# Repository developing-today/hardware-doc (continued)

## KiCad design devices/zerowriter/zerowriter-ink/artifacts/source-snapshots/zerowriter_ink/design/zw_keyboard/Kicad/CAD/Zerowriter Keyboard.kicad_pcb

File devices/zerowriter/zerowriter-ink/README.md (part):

# ZeroWriter Ink

> Open-source e-paper typewriter · Crowd Supply campaign funded **2024-10-17** · **$285** · 585 backers · $147,538 raised (491 % of a $30,000 goal)
> By **Adam Wilk** / Zerowriter, Ottawa, Canada, in collaboration with **Soldered Electronics** (Osijek, Croatia)
> Research snapshot **2026-08-24**

A distraction-free writing device: a 5.2" 1280×720 e-paper display, a hot-swappable 60 % mechanical keyboard, and firmware that boots straight into a text file. No cloud, no accounts, no wireless enabled by default.

---

## The single most important architectural fact

**ZeroWriter Ink contains two ESP32s.**

| Board | Processor | Role |
|---|---|---|
| **Zerowriter Inkplate 5 Gen2** (main board) | **ESP32-WROVER** | Display, storage, RTC, application firmware |
| **Zerowriter Keyboard** (keyboard PCB) | **ESP32-WROOM-32U-N4** | Key-matrix scanning, its own firmware |

This is recovered from the two KiCad BOMs in the project's own repository ([`design/src/`](artifacts/source-snapshots/zerowriter_ink/design/src/)) and is **not stated anywhere in the campaign material or the README**, which describe the device as "built around the ubiquitous ESP32 module" — singular. If you are planning firmware work, you need to know there are two independent targets joined by a cable.

The keyboard PCB carries a `NOVA_programmer_header` (6-pin) and connects to the main board through a **`HC-1.25-6PWT` 6-pin connector**, which strongly suggests a serial link rather than a scanned matrix crossing the cable — 61 × `1N4148W` matrix diodes are on the *keyboard* board, so the matrix is decoded locally.

> Evidence status: the two-processor split is **established from primary design files**. The *protocol* between them is **inferred** from connector pin count and the placement of the matrix diodes — not confirmed from source.

---

## The second important fact: this is not a stock Inkplate 5

ZeroWriter's main board is a **respin** of Soldered's Inkplate 5 Gen 2, not the off-the-shelf product. Comparing the two BOMs designator-by-designator ([Soldered Gen 2](../../soldered-electronics/inkplate-5-gen2/README.md) vs [ZeroWriter's variant](artifacts/source-snapshots/zerowriter_ink/design/src/)) shows **8 added parts, 14 removed, and 20 changed values**.

### Which Inkplate generation? — **Gen 2**, confirmed five ways

Worth stating plainly, because the campaign's early material described a different panel (see below).

| Evidence | Result |
|---|---|
| ZeroWriter BOM, `U9` | **`ED052TC4`** |
| Soldered Inkplate 5 **Gen 2** BOM, `U9` | `ED052TC4` ✅ match |
| Soldered Inkplate 5 (gen 1) BOM, `U11` | `ED052TC2` ❌ different part *and* different designator |
| ZeroWriter's KiCad project name | `Zerowriter Inkplate 5 **Gen2**.kicad_pro` |
| Crowd Supply spec | "**second-edition** Inkplate 5.2" display with an upgraded **1280 × 720** widescreen resolution" |
| Campaign update, Nov 2024 | "we jumped on their **new generation panel: Inkplate 5v2**" |

`ED052TC4` ⇒ **1280 × 720** (`ARDUINO_INKPLATE5V2`). The gen-1 `ED052TC2` is 960 × 540.

#### ⚠ The panel changed mid-project

If you recall the ZeroWriter Ink being a **gen-1** Inkplate 5, that was true of the **development prototype**. The developer describes the switch in the Nov 2024 post-funding update:

> When it came to Zerowriter Ink, **we jumped on their new generation panel: Inkplate 5v2**… The downside? … The new panels looked great, but operated at about 200 ms. This was **a decent chunk slower than the panel I'd been developing into Zerowriter Ink**…

So the sequence was: prototype on the **gen-1 panel** → switch to **Gen 2** for the higher resolution → discover it is slower → commission [bitbank2's optimisation work](development-history.md#the-e-paper-latency-problem-and-how-it-was-solved) to get from ~200 ms to ~100 ms.

**The shipping product is Gen 2.** Pre-funding material describing a 960 × 540 panel is describing the prototype.

### "Minor tweaks" is an understatement

The respin is not a light touch. Designator-by-designator against Soldered's stock Gen 2: **8 parts added, 14 removed, 20 values changed**, including a complete charger redesign and relocation of USB-C and microSD to a separate board.

What *is* unchanged is the part that matters for software: **all 36 connected ESP32 pads carry identical net names** ([verified](../../soldered-electronics/inkplate-5-gen2/README.md#zerowriter-compatibility)), so the Inkplate Arduino library applies. That is probably the origin of the "minor tweaks" impression — from a firmware perspective it behaves like a stock Gen 2; from a hardware perspective it is substantially reworked.

### The charger was completely redesigned

| | Soldered Inkplate 5 Gen 2 | **ZeroWriter variant** |
|---|---|---|
| Charger IC | `MCP73831T` — **linear** | **`BQ25306RTER`** — TI **switch-mode** buck charger |
| Inductor | — | **`L3 = SRP3212A-1R0M`** (1 µH) added |
| Support caps | — | `C58` 4u7, `C59` 2u2, `C60`/`C61` 10u, `C62` 470p added |
| `U4` position | `MCP73831T` (charger) | **`USBLC6-2SC6`** — USB ESD protection |

A linear charger dissipates `(Vin − Vbat) × Icharge` as heat, which caps practical charge current on a small board. Swapping to a switch-mode `BQ25306` is exactly what you do when you fit a much larger cell and want it charged in reasonable time without cooking the PCB. This is consistent with the campaign's "up to weeks of daily use" and ~100 hour battery-life claim.

### Connectors moved off the display board

| Ref | Soldered Gen 2 | ZeroWriter variant | Reading |
|---|---|---|---|
| `K2` | `U262-161N-4BVC11` (**USB-C receptacle**) | `HC-1.25-6PWT` (**6-pin wire-to-board**) | USB-C is **not on the display board** — it moves to the separate breakout PCB |
| `K1` | — | `HC-1.25-16PWT` (**16-pin**) added | New inter-board link |
| `K3` | `easyC-SMD` | `qwiic-SMD` | Same physical connector, renamed. Soldered's *easyC* is pin-compatible with SparkFun *Qwiic* / Adafruit *STEMMA QT* |
| `K10` | `HYC77-TF09-200` (**microSD socket**) | *removed* | microSD relocated off the display board |

### Parts removed

`U5` (`MC14093BDTR2G` quad Schmitt NAND), `F1` (500 mA fuse), `D8`/`D9` (LEDs), `SW2` (button), `S1` (slide switch), `Q8`/`Q9`, and test points `TP60`–`TP63`. Plus ~20 resistor/capacitor value changes clustered around the power and charging sections.

**Consequence for hackers:** a stock Inkplate 5 Gen 2 is *close* to the ZeroWriter main board but not identical. Firmware written against the Inkplate Arduino library should work (same ESP32-WROVER, same `ED052TC4` panel, same `TPS65186` PMIC, same `PCAL6416A` expander, same `PCF85063A` RTC), but **power, charging, USB and SD paths differ** — do not assume battery or SD behaviour transfers.

---

## Architecture

```
┌─ Zerowriter Keyboard PCB ──────────────────────────────┐
│ ESP32-WROOM-32U-N4  (external-antenna variant)         │
│ 61 × 1N4148W matrix diodes                             │
│ Kailh Choc v1 hot-swap sockets (CPG135001S30)          │
│   incl. 1.2u / 1.5u / 1.7u / 2u / 6.25u stabilised keys│
│ RST1/RST2 tactiles · NOVA 6-pin programmer header      │
└────────────── HC-1.25-6PWT (6-pin) ────────────────────┘
                       │
┌─ Zerowriter Inkplate 5 Gen2 (main) ────────────────────┐
│ ESP32-WROVER              U11                          │
│ ED052TC4  5.2" 1280×720 e-paper   U9                   │
│ TPS65186RGZ  e-paper PMIC          U1                  │
│ PCAL6416AHF  16-bit I²C GPIO expander @ 0x20  U10      │
│ PCF85063A    RTC                    U7                 │
│ CH340C       USB-UART               U3                 │
│ BQ25306RTER  switch-mode Li-ion charger  U12  [ZW-only]│
│ TPS7A2633    3V3 LDO · TPS3840 supervisor              │
│ qwiic/easyC I²C connector                              │
└──── HC-1.25-16PWT (16-pin) ────────────────────────────┘
                       │
┌─ Zerowriter breakout board ────────────────────────────┐
│ USB-C, microSD (relocated from the display board)      │
└────────────────────────────────────────────────────────┘
```

Component records: [ESP32-WROVER](../../../components/espressif/esp32-wrover/README.md) · [ESP32-WROOM-32U](../../../components/espressif/esp32-wroom-32u/README.md) · [TPS65186](../../../components/texas-instruments/tps65186/README.md) · [PCAL6416A](../../../components/nxp/pcal6416a/README.md) · [PCF85063A](../../../components/nxp/pcf85063a/README.md) · [BQ25306](../../../components/texas-instruments/bq25306/README.md) · [CH340C](../../../components/wch/ch340c/README.md) · [ED052TC4 panel](../../../components/e-ink/ed052tc4/README.md)

## Specifications

| | |
|---|---|
| Display | **Inkplate 5 Gen 2 panel — `ED052TC4`, 5.2", 1280 × 720** e-paper |
| Keyboard | 60 %, hot-swappable, **Kailh Choc Pro Red** low-profile switches, US English legends, optional arrow-key mod |
| Languages | Extended ASCII 256 — English, French, German, Spanish, Italian and other western/latin scripts |
| Dimensions | **300 × 195 × 15 mm** (12 × 7.5 × 0.6 in) — fits most 13" laptop sleeves |
| Storage | microSD (user files), plus firmware update via SD |
| Connectivity | USB-C (charging + UART file transfer via companion app); **QR-code transfer to phone**; Wi-Fi/BLE present in silicon but **not enabled in shipped firmware** |
| Battery | Built-in, **user-replaceable** LiPo; ~100 h claimed |
| Document limit | **3,000 lines (~24,000 words)** per document |
| Firmware | Arduino-based ("Zerowriter Core"). Repo releases end at **1.30**; **current is v2.1 (July 2026)**, website-only — see [`community-and-ecosystem.md`](community-and-ecosystem.md#-the-repository-firmware-is-two-major-versions-behind) |
| Enclosure | Custom; STLs in-repo (`zw_tophousing.stl`, `zw_bottomhousing.stl`) |

**On wireless:** the campaign is explicit that shipping without wireless was a deliberate cost/certification decision — "less development time, less red-tape, and less cost to you" — not a hardware limitation. Note the keyboard uses a **WROOM-32U**, the *external antenna* variant, which has no PCB antenna at all. Enabling radio on either processor is a project, not a config flag.

## Vendor comparison (from the campaign)

| | Zerowriter Ink | Pomera DM30 | Alphasmart Neo | Freewrite Alpha | Freewrite Traveler |
|---|---|---|---|---|---|
| Display | **HD e-paper** | e-paper | LCD | LCD | e-paper |
| Cloud | Not by default | No | No | Yes | Yes |
| Availability | **New** | Used | Used | New | New |
| Mechanical keyboard | **Yes, hot-swap** | No | No | Yes | No |
| Battery (claimed) | 100 h | 20 h | **700 h** | 100 h | 4 weeks |
| Open source | **Yes** | No | No | No | No |

Vendor-authored comparison — treat as marketing. The Alphasmart Neo's 700 hours on AA cells is the honest outlier and the standard this class of device is measured against.

## Lineage

The **original ZeroWriter** ([`zerowriter/zerowriter1`](artifacts/source-snapshots/zerowriter1/), 367★, MIT) was a Raspberry Pi Zero + cheap e-paper DIY project. ZeroWriter Ink is a ground-up redesign on the Inkplate 5 — a different processor family, a different display, and a commercial product rather than a build-it-yourself guide. The two share a name and a goal, not a codebase.

## Website: zerowriter.**ink**, not .com

⚠ **`zerowriter.com` is a domain-for-sale parking page** (Spaceship.com, $7,500) and is *not* the project. The Crowd Supply campaign links to it, so it is an easy trap.

**The live site is <https://zerowriter.ink>.** Found via a URL embedded in the firmware release notes shipped in the GitHub repo (`firmware_releases/updates-readme.txt` points at `zerowriter.ink/pages/firmware-updates`), not from any link on the campaign page.

The live site reveals a **second product**: the **Zerowriter Fold**, funded via Kickstarter and shipping after the Ink.

| Source | URL | Status |
|---|---|---|
| **Official site** | <https://zerowriter.ink> | **Live** |
| Firmware updates + web flasher | <https://zerowriter.ink/pages/firmware-updates> | **Live** |
| News blog | <https://zerowriter.ink/blogs/news> | Live |
| Zerowriter Fold | <https://zerowriter.ink/pages/zerowriter-fold> | Live |
| Crowd Supply campaign | <https://www.crowdsupply.com/zerowriter/zerowriter-ink> | Live |
| GitHub (main) | <https://github.com/zerowriter/zerowriter_ink> | Live, GPL-3.0 |
| GitHub (original Pi project) | <https://github.com/zerowriter/zerowriter1> | Live, MIT |
| Discord | <https://discord.gg/57yANTWGet> | Live |
| **Reddit** | <https://www.reddit.com/r/zerowriter/> | Live — official support channel |
| `zerowriter.com` | — | **Parked / for sale. Not the project.** |

> **Retrieval trap:** `zerowriter.ink` returns **403 to a normal Chrome user agent** but **200 to the ClaudeBot UA**. See the [vendor guide](../../../vendors/zerowriter/README.md).

## Press coverage

Tom's Hardware · Liliputing · Boing Boing · Yanko Design · Notebookcheck (DE) · CircuitDigest · TechEBlog · Good e-Reader · e-ink-info · ereaderpro.co.uk · pascalforget.com — full URLs in [`sources.md`](sources.md).

## Repository contents (preserved)

```
artifacts/source-snapshots/zerowriter_ink/     GPL-3.0, commit 996207ac (2026-05-13)
├── design/
│   ├── src/Zerowriter Inkplate 5 Gen2/v1.2.0/   KiCad: main board respin
│   ├── src/Zerowriter Keyboard/v1.2.0/          KiCad: keyboard + ESP32-WROOM-32U
│   ├── src/Zerowriter breakout board/           gerbers: USB-C + microSD
│   ├── zw_keyboard/                             plate DXF, gerbers, schematic PDF
│   └── enclosure/                               zw_tophousing.stl, zw_bottomhousing.stl
├── firmware_releases/                           SD-1.3, archived updates, CLI tools
├── compiled fonts/                              .bbf bitmap fonts
├── src/keyboard/                                keyboard firmware source
└── utils/
artifacts/source-snapshots/zerowriter1/        MIT, commit e476d056 — the Pi Zero original
```

### Size cleanup — what was moved out (2026-08-24)

Two things were archived out of this tree. **Both left a placeholder in situ** carrying digests and
reacquisition commands, and neither is unique:

| Removed | Size | Placeholder | Why it was safe |
|---|---:|---|---|
| `zerowriter1/e-Paper/` — Waveshare's vendored Python driver library | 31.07 MiB, 272 files | [`e-Paper.ARCHIVED.md`](artifacts/source-snapshots/zerowriter1/e-Paper.ARCHIVED.md) | 270 of 272 files byte-identical to Waveshare upstream; the 2 that differ are preserved as patches |
| 4 × KiCad `*-backups/` auto-save ZIP directories | 27.27 MiB, 15 files | one `*.ARCHIVED.md` beside each | editor crash-recovery snapshots of designs that are still present, uncompressed, alongside |

**No design file, firmware image or ZeroWriter-authored source was removed.** All 15 backup ZIPs
are present in the archive and recoverable verbatim from upstream commit `996207ac`
(re-verified **2026-09-20**, see below).

> ⚠ **Corrected 2026-09-20.** This section previously asserted that the entire `zerowriter_ink`
> snapshot "was verified **byte-identical** to upstream commit `996207ac`". That was true when
> written on 2026-08-24 and **is no longer true of the tree today**: on 2026-08-30 an in-repo pass
> normalised **50 of the snapshot's 152 files** — 36 CRLF → LF, 14 trailing-whitespace-stripped.
> **Zero semantic differences** were introduced, so every pinout, net and BOM row read out of these
> files remains sound; but `diff -rq` and raw SHA-256 comparison against upstream will now report
> 50 false positives, and an in-repo file hash must not be cited as upstream identity.
> Full file-by-file breakdown, cause analysis and the correct comparison recipe:
> **[`source-snapshot-provenance.md`](source-snapshot-provenance.md)**.
>
> The same document records that three of the four `*-backups/` directories had been lost from the
> archive (a later pass archived their parent `PANEL/` onto the same path) and survived only in
> `scratch/`. They were moved back into the archive on 2026-09-20 and verified by fingerprint.

- [`artifacts/vendored-deps/README.md`](artifacts/vendored-deps/README.md) — removed-dependency register: digests, licenses, verified download URLs
- [`zerowriter1-epaper-driver-notes.md`](zerowriter1-epaper-driver-notes.md) — **what ZeroWriter changed in the Waveshare driver, and why it matters**
- [`source-snapshot-provenance.md`](source-snapshot-provenance.md) — **what is and is not byte-identical to upstream in this snapshot**, and how to compare it correctly

## Related

- [Inkplate 5 / Gen 2](../../soldered-electronics/inkplate-5/README.md) — the display platform this is built on
- [Soldered Electronics vendor guide](../../../vendors/soldered-electronics/README.md)
- [All devices](../../README.md)
- [`keyboard.md`](keyboard.md) — the second ESP32, wire protocol, matrix
- [`inter-board-wiring.md`](inter-board-wiring.md) — both connector pinouts, breakout board BOM
- [`keymap-format.md`](keymap-format.md) — `keymap.json`, full default layout
- [`software-and-shortcuts.md`](software-and-shortcuts.md) — shortcuts, Core 1.1, release timeline
- [`community-and-ecosystem.md`](community-and-ecosystem.md) — **firmware v2.1**, third-party firmware, owner reports
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
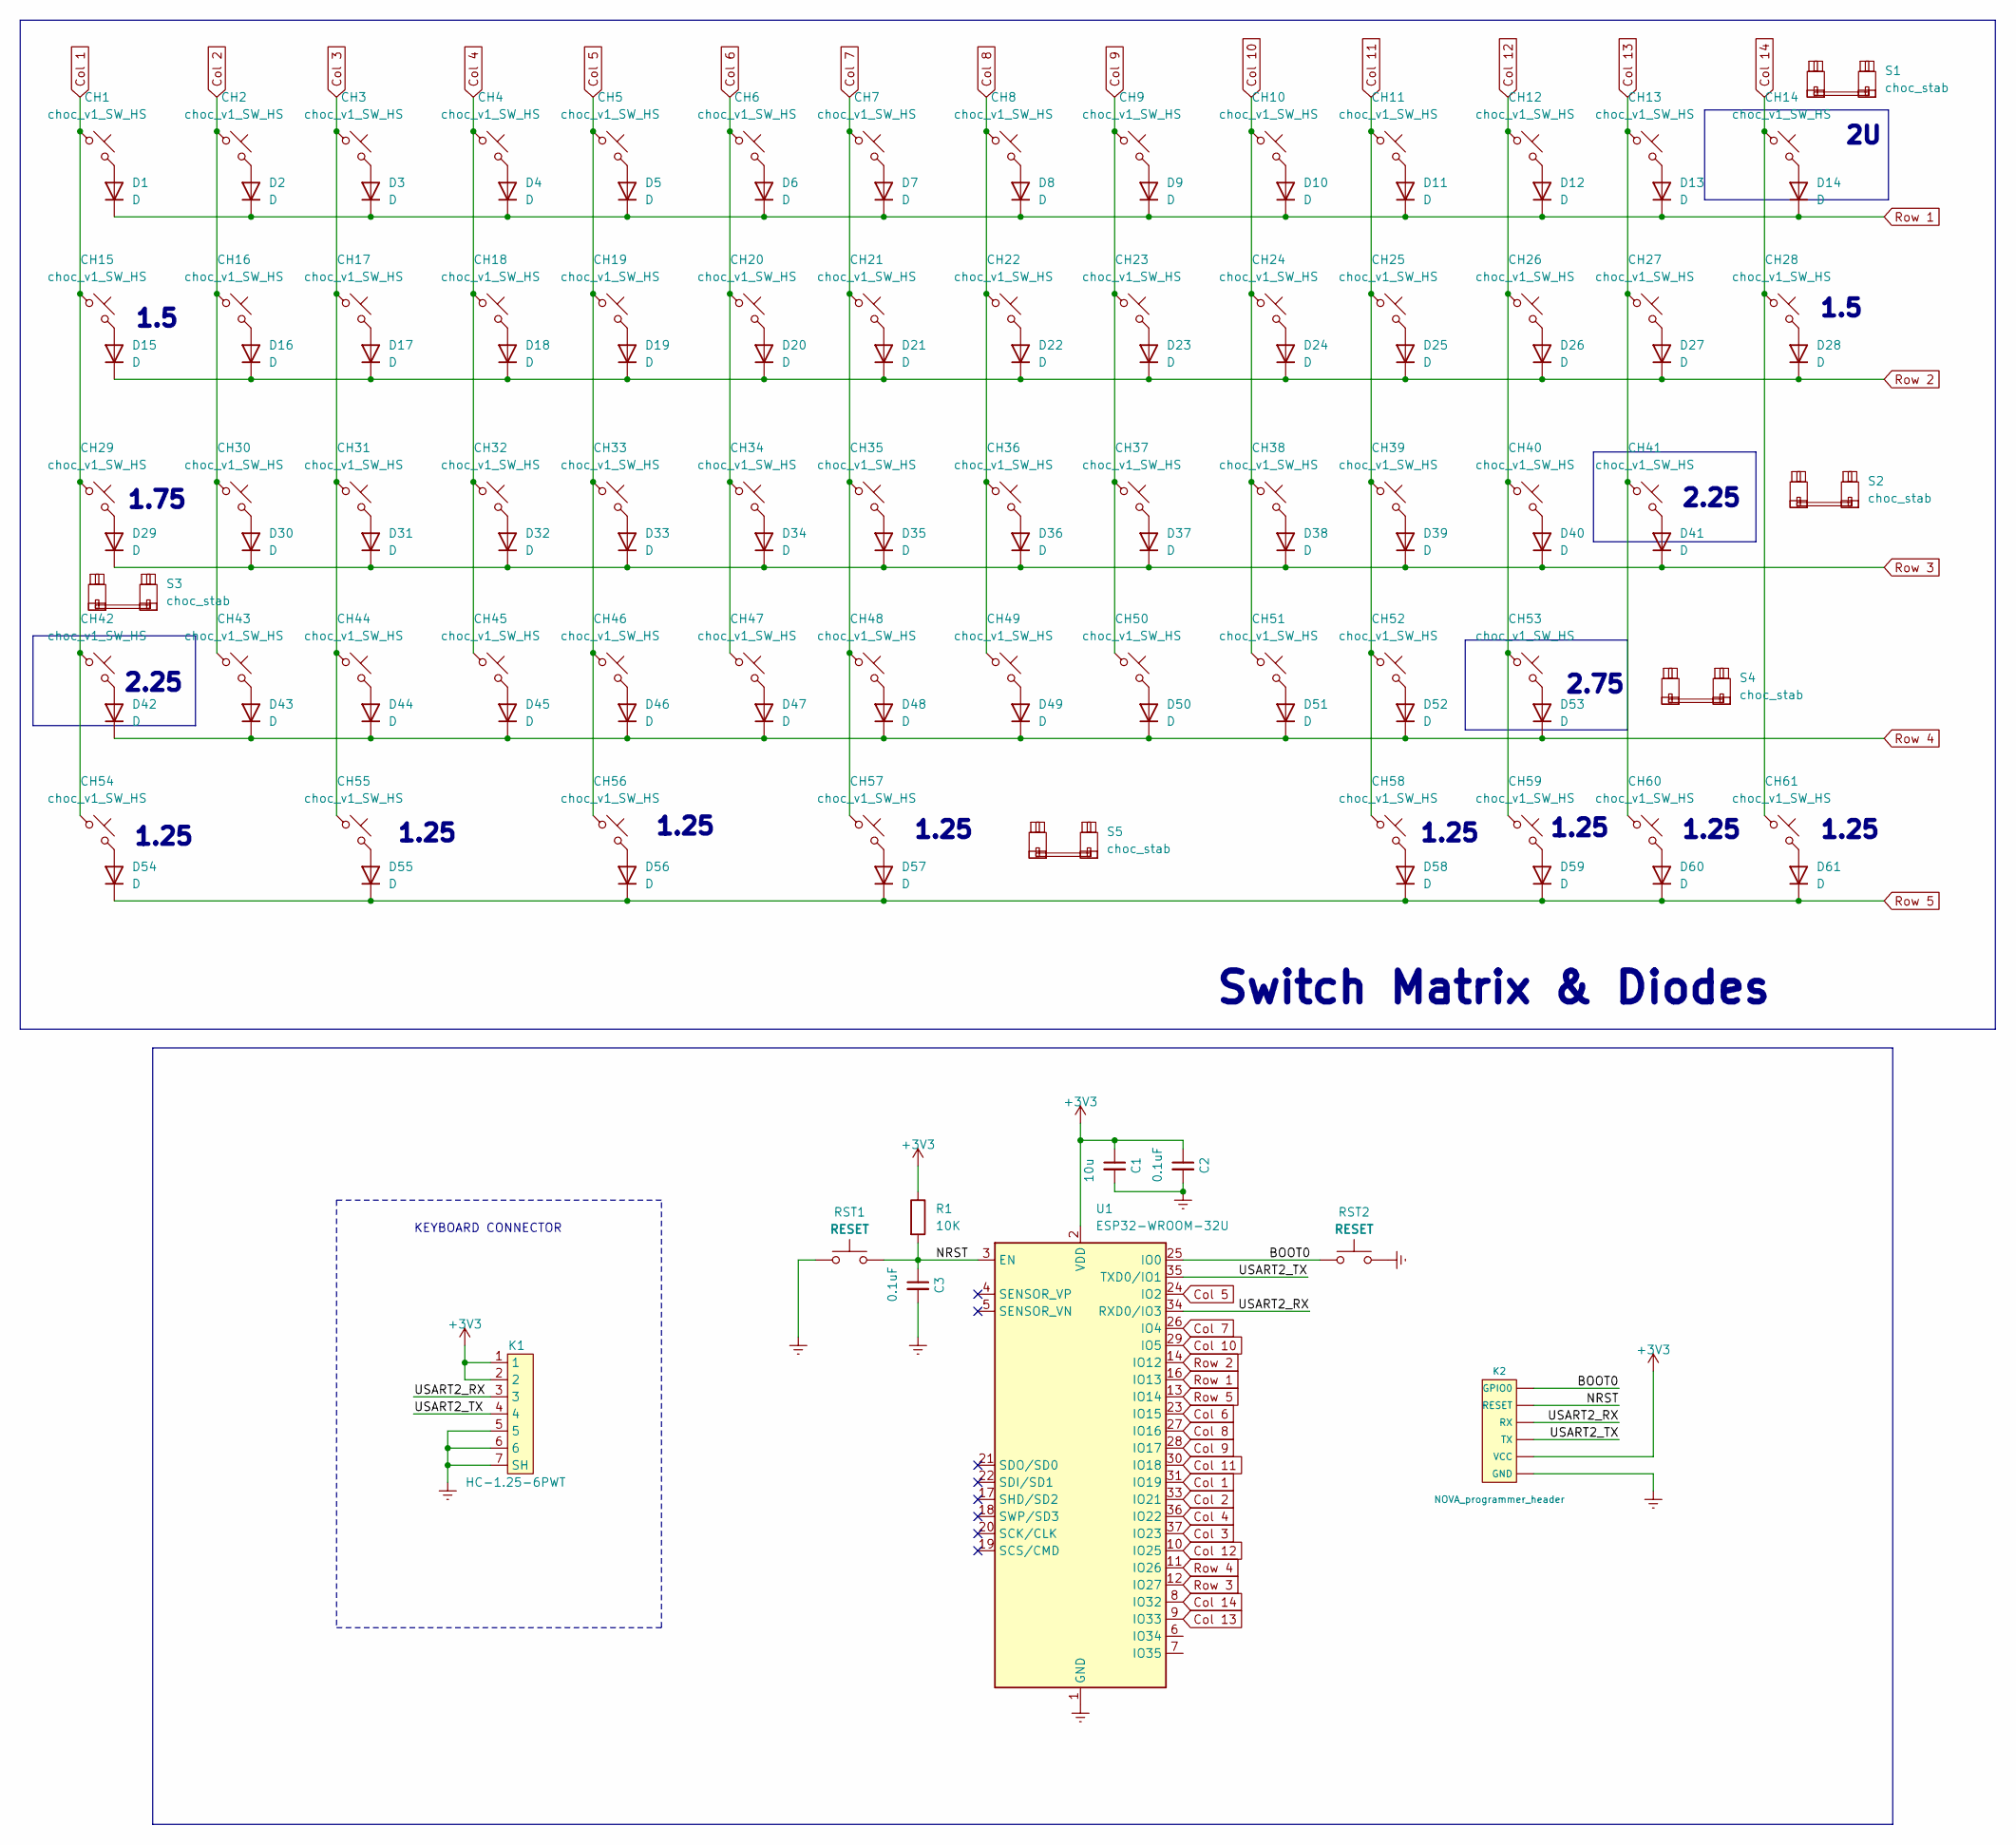
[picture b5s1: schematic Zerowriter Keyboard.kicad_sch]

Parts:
C1: 10u; C_0402_1005Metric_Pad0.74x0.62mm_HandSolder; JLCPCB part# C1557
C2, C3: 0.1uF; C_0402_1005Metric_Pad0.74x0.62mm_HandSolder; JLCPCB part# C1557
CH1, CH2, CH3, CH4, CH5, CH6, CH7, CH8, CH9, CH10, CH11, CH12, CH13, CH14, CH16, CH17, CH18, CH19, CH20, CH21, CH22, CH23, CH24, CH25, CH26, CH27, CH30, CH31, CH32, CH33, CH34, CH35, CH36, CH37, CH38, CH39, CH40, CH41, CH42, CH43, CH44, CH45, CH46, CH47, CH48, CH49, CH50, CH51, CH52, CH53: choc_v1_SW_HS; SW_choc_v1_HS_CPG135001S30_1u_custom; JLCPCB part# C5333465
CH15, CH28: choc_v1_SW_HS; SW_choc_v1_HS_CPG135001S30_1.5u_custom; JLCPCB part# C5333465
CH29: choc_v1_SW_HS; SW_choc_v1_HS_CPG135001S30_1.75u_custom; JLCPCB part# C5333465
CH54, CH55, CH56, CH57, CH58, CH59, CH60, CH61: choc_v1_SW_HS; SW_choc_v1_HS_CPG135001S30_1.25u_custom; JLCPCB part# C5333465
D1, D2, D3, D4, D5, D6, D7, D8, D9, D10, D11, D12, D13, D14, D15, D16, D17, D18, D19, D20, D21, D22, D23, D24, D25, D26, D27, D28, D29, D30, D31, D32, D33, D34, D35, D36, D37, D38, D39, D40, D41, D42, D43, D44, D45, D46, D47, D48, D49, D50, D51, D52, D53, D54, D55, D56, D57, D58, D59, D60, D61: D; D_SOD-123; JLCPCB part# C2099
K1: HC-1.25-6PWT
K2: NOVA_programmer_header; HEADER_MALE_6X1
R1: 10K; R_0603_1608Metric; JLCPCB part# C25804
RST1, RST2: RESET; SW_SPST_SKQG_WithStem; JLCPCB part# C5140332
S1, S2, S3, S4: choc_stab; STAB_choc_2u; JLCPCB part# DNP
S5: choc_stab; Choc-6.25u-cutout; JLCPCB part# DNP
U1: ESP32-WROOM-32U; JLCPCB part# C328062

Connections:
+3V3: C1.1, C2.1, K1.1, K1.2, K2.2 (VCC), R1.1, U1.2 (VDD)
/BOOT0: K2.6 (GPIO0), RST2.1, U1.25 (IO0)
/NRST: C3.1, K2.5 (RESET), R1.2, RST1.2, U1.3 (EN)
/USART2_RX: K1.3, K2.4 (RX), U1.34 (RXD0/IO3)
/USART2_TX: K1.4, K2.3 (TX), U1.35 (TXD0/IO1)
Col 1: CH1.1, CH15.1, CH29.1, CH42.1, CH54.1, U1.31 (IO19)
Col 2: CH2.1, CH16.1, CH30.1, CH43.1, U1.33 (IO21)
Col 3: CH3.1, CH17.1, CH31.1, CH44.1, CH55.1, U1.37 (IO23)
Col 4: CH4.1, CH18.1, CH32.1, CH45.1, U1.36 (IO22)
Col 5: CH5.1, CH19.1, CH33.1, CH46.1, CH56.1, U1.24 (IO2)
Col 6: CH6.1, CH20.1, CH34.1, CH47.1, U1.23 (IO15)
Col 7: CH7.1, CH21.1, CH35.1, CH48.1, CH57.1, U1.26 (IO4)
Col 8: CH8.1, CH22.1, CH36.1, CH49.1, U1.27 (IO16)
Col 9: CH9.1, CH23.1, CH37.1, CH50.1, U1.28 (IO17)
Col 10: CH10.1, CH24.1, CH38.1, CH51.1, U1.29 (IO5)
Col 11: CH11.1, CH25.1, CH39.1, CH52.1, CH58.1, U1.30 (IO18)
Col 12: CH12.1, CH26.1, CH40.1, CH53.1, CH59.1, U1.10 (IO25)
Col 13: CH13.1, CH27.1, CH41.1, CH60.1, U1.9 (IO33)
Col 14: CH14.1, CH28.1, CH61.1, U1.8 (IO32)
Earth: C1.2, C2.2, C3.2, K1.5, K1.6, K1.7 (SH), K2.1 (GND), RST1.1, RST2.2, U1.1 (GND), U1.15 (GND), U1.38 (GND), U1.39 (GND)
unnamed: CH1.2, D1.2 (A)
unnamed: CH2.2, D2.2 (A)
unnamed: CH3.2, D3.2 (A)
unnamed: CH4.2, D4.2 (A)
unnamed: CH5.2, D5.2 (A)
unnamed: CH6.2, D6.2 (A)
unnamed: CH7.2, D7.2 (A)
unnamed: CH8.2, D8.2 (A)
unnamed: CH9.2, D9.2 (A)
unnamed: CH10.2, D10.2 (A)
unnamed: CH11.2, D11.2 (A)
unnamed: CH12.2, D12.2 (A)
unnamed: CH13.2, D13.2 (A)
unnamed: CH14.2, D14.2 (A)
unnamed: CH15.2, D15.2 (A)
unnamed: CH16.2, D16.2 (A)
unnamed: CH17.2, D17.2 (A)
unnamed: CH18.2, D18.2 (A)
unnamed: CH19.2, D19.2 (A)
unnamed: CH20.2, D20.2 (A)
unnamed: CH21.2, D21.2 (A)
unnamed: CH22.2, D22.2 (A)
unnamed: CH23.2, D23.2 (A)
unnamed: CH24.2, D24.2 (A)
unnamed: CH25.2, D25.2 (A)
unnamed: CH26.2, D26.2 (A)
unnamed: CH27.2, D27.2 (A)
unnamed: CH28.2, D28.2 (A)
unnamed: CH29.2, D29.2 (A)
unnamed: CH30.2, D30.2 (A)
unnamed: CH31.2, D31.2 (A)
unnamed: CH32.2, D32.2 (A)
unnamed: CH33.2, D33.2 (A)
unnamed: CH34.2, D34.2 (A)
unnamed: CH35.2, D35.2 (A)
unnamed: CH36.2, D36.2 (A)
unnamed: CH37.2, D37.2 (A)
unnamed: CH38.2, D38.2 (A)
unnamed: CH39.2, D39.2 (A)
unnamed: CH40.2, D40.2 (A)
unnamed: CH41.2, D41.2 (A)
unnamed: CH42.2, D42.2 (A)
unnamed: CH43.2, D43.2 (A)
unnamed: CH44.2, D44.2 (A)
unnamed: CH45.2, D45.2 (A)
unnamed: CH46.2, D46.2 (A)
unnamed: CH47.2, D47.2 (A)
unnamed: CH48.2, D48.2 (A)
unnamed: CH49.2, D49.2 (A)
unnamed: CH50.2, D50.2 (A)
unnamed: CH51.2, D51.2 (A)
unnamed: CH52.2, D52.2 (A)
unnamed: CH53.2, D53.2 (A)
unnamed: CH54.2, D54.2 (A)
unnamed: CH55.2, D55.2 (A)
unnamed: CH56.2, D56.2 (A)
unnamed: CH57.2, D57.2 (A)
unnamed: CH58.2, D58.2 (A)
unnamed: CH59.2, D59.2 (A)
unnamed: CH60.2, D60.2 (A)
unnamed: CH61.2, D61.2 (A)
Row 1: D1.1 (K), D2.1 (K), D3.1 (K), D4.1 (K), D5.1 (K), D6.1 (K), D7.1 (K), D8.1 (K), D9.1 (K), D10.1 (K), D11.1 (K), D12.1 (K), D13.1 (K), D14.1 (K), U1.16 (IO13)
Row 2: D15.1 (K), D16.1 (K), D17.1 (K), D18.1 (K), D19.1 (K), D20.1 (K), D21.1 (K), D22.1 (K), D23.1 (K), D24.1 (K), D25.1 (K), D26.1 (K), D27.1 (K), D28.1 (K), U1.14 (IO12)
Row 3: D29.1 (K), D30.1 (K), D31.1 (K), D32.1 (K), D33.1 (K), D34.1 (K), D35.1 (K), D36.1 (K), D37.1 (K), D38.1 (K), D39.1 (K), D40.1 (K), D41.1 (K), U1.12 (IO27)
Row 4: D42.1 (K), D43.1 (K), D44.1 (K), D45.1 (K), D46.1 (K), D47.1 (K), D48.1 (K), D49.1 (K), D50.1 (K), D51.1 (K), D52.1 (K), D53.1 (K), U1.11 (IO26)
Row 5: D54.1 (K), D55.1 (K), D56.1 (K), D57.1 (K), D58.1 (K), D59.1 (K), D60.1 (K), D61.1 (K), U1.13 (IO14)

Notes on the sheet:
1.25
KEYBOARD CONNECTOR
2.75
2.25
Switch Matrix & Diodes
1.5
1.75
1.5

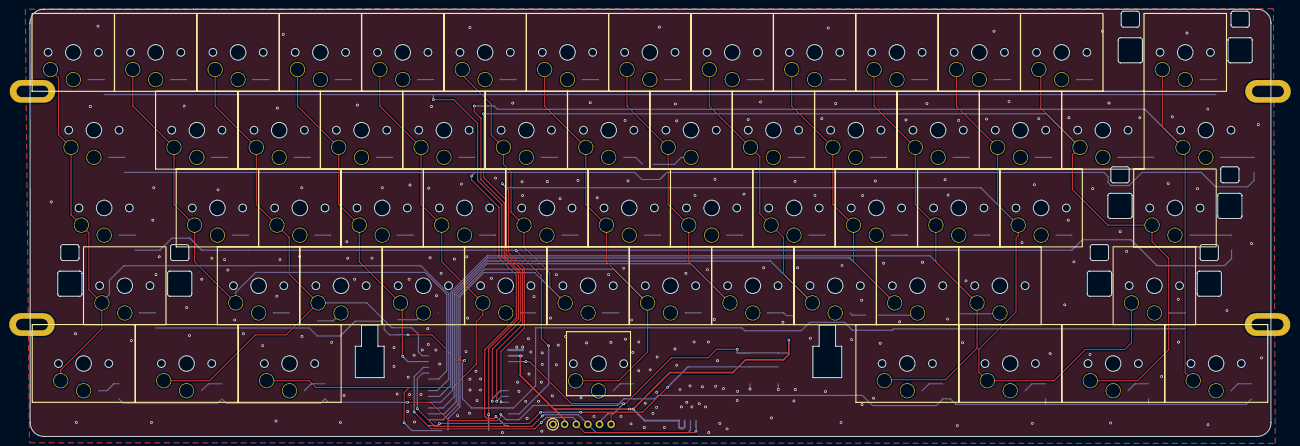
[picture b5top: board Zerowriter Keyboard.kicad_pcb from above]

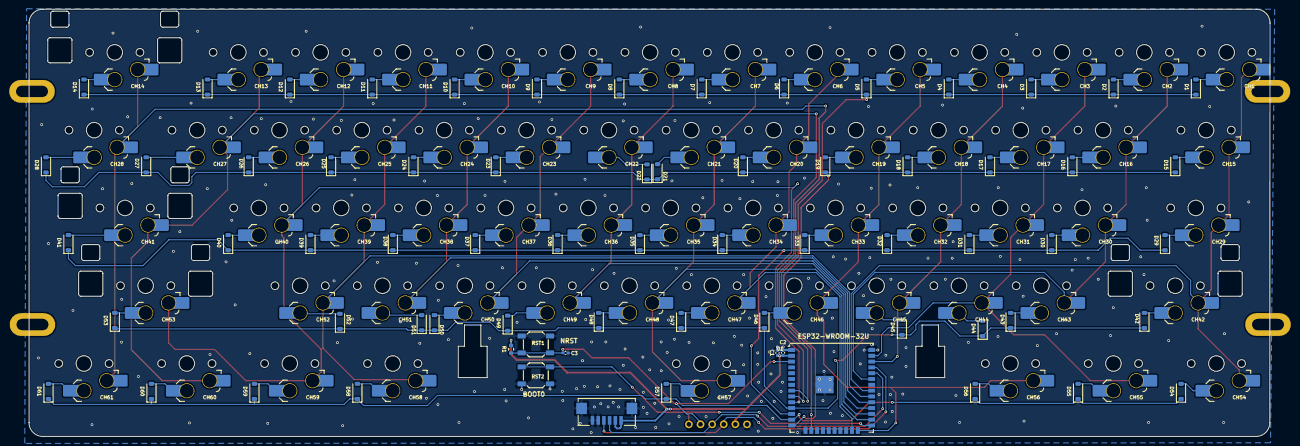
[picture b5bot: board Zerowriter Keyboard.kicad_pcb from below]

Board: 2 copper layers, 271.2 x 93.3 mm, 136 parts (135 on the bottom side), 86 nets.

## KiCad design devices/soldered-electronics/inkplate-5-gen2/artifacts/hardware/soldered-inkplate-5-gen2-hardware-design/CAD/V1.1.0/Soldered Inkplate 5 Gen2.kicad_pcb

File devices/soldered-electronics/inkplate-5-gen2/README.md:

# Soldered Inkplate 5 Gen 2

> 5.2" **1280 × 720** e-paper development board, ESP32-WROVER. Hardware design rev **V1.1.0**, TAPR OHL.
> Arduino board target: **`Inkplate5V2`**. Research snapshot **2026-08-24**.

**The full technical record for both generations lives in [`../inkplate-5/README.md`](../inkplate-5/README.md).** This page exists so the Gen 2 is findable by name and records what is specific to it.

> **Note on scope:** this generation was documented from primary design files and library source, but **no physical unit was available** and it was researched as the display platform underneath [ZeroWriter Ink](../../zerowriter/zerowriter-ink/README.md) rather than as a board in its own right. Treat this as a solid overview, not an exhaustive record.

## What is different from the Inkplate 5

Exactly one component. Both BOMs were parsed and compared designator-by-designator:

| | Inkplate 5 | **Inkplate 5 Gen 2** |
|---|---|---|
| Panel | `ED052TC2` *(no component record)* | **[`ED052TC4`](../../../components/e-ink/ed052tc4/README.md)** |
| Resolution | 960 × 540 (518,400 px) | **1280 × 720 (921,600 px)** |
| Pixel count | — | **+78 %** at the same 5.2" diagonal |
| Design rev | V1.2.0 | V1.1.0 |
| Arduino define | `ARDUINO_INKPLATE5` | `ARDUINO_INKPLATE5V2` |

Identical: **[ESP32-WROVER](../../../components/espressif/esp32-wrover/README.md)**,
[`TPS65186RGZ`](../../../components/texas-instruments/tps65186/README.md) EPD PMIC,
[`PCAL6416AHF`](../../../components/nxp/pcal6416a/README.md) I/O expander @ 0x20,
[`PCF85063A`](../../../components/nxp/pcf85063a/README.md) RTC,
[`CH340C`](../../../components/wch/ch340c/README.md) USB-UART, `MCP73831T` charger,
`TPS7A2633` LDO, `TPS3840` supervisor, `SN74LVC1G34`, `MC14093B`, NTC temperature sense,
[microSD](../../../components/generic/micro-sd-sdmmc/README.md), easyC/Qwiic connector.

Parts named without a link have **no record** under [`components/`](../../../components/README.md) —
see [the Inkplate 5 BOM table](../inkplate-5/README.md#complete-bill-of-materials-inkplate-5-v120).

Designator numbering shifts slightly between the two (the ESP32 is `U10` on the Inkplate 5 and `U11` on the Gen 2; the panel is `U11` then `U9`), so do not match parts across the two BOMs by reference designator alone.

Resolutions confirmed from `Inkplate-Arduino-library/src/boards/Inkplate5V2/waveforms.h`:

```c
#define E_INK_WIDTH  1280
#define E_INK_HEIGHT 720
```

## Pin map verified identical to the Inkplate 5

**Verified 2026-08-24** by netlist-parsing the Gen 2's own `.kicad_pcb` and diffing the ESP32-WROVER pad-to-net mapping against the Inkplate 5. **All 36 connected pads carry the same net names.** The Gen 2 is genuinely a panel swap — the processor wiring is untouched.

Full pin table: [`../inkplate-5/pinouts-and-buses.md`](../inkplate-5/pinouts-and-buses.md). It applies to this board without modification.

The same comparison against **ZeroWriter's respun variant** also shows an identical ESP32 pin map — see [§ ZeroWriter compatibility](#zerowriter-compatibility).

## Why the higher resolution costs you something

The [ESP32-WROVER](../../../components/espressif/esp32-wrover/README.md)'s PSRAM is what makes this panel viable — a 1280 × 720 buffer is 921,600 px, which at 1 bit per pixel is 115 KB and at 4 bits (greyscale) is **450 KB**. The Arduino driver allocates both a `_partial` 1-bit buffer and a `DMemory4Bit` greyscale buffer:

```c
memset(_partial,    0,   E_INK_WIDTH * E_INK_HEIGHT / 8);   // 115,200 B
memset(DMemory4Bit, 255, E_INK_WIDTH * E_INK_HEIGHT / 2);   // 460,800 B
```

That is comfortably beyond the ESP32's internal RAM and is why every Inkplate uses a **WROVER** (PSRAM) module rather than a WROOM. It also means refresh times are longer than the Inkplate 5's — more data to clock out over the same I2S1 parallel bus.

## ZeroWriter compatibility

[ZeroWriter Ink](../../zerowriter/zerowriter-ink/README.md) ships a **respun** version of this board. Diffing the ESP32-WROVER net map between Soldered's stock Gen 2 and ZeroWriter's variant:

**Every connected pad is identical.** The only differences are cosmetic labels on the six *unconnected* module pads:

| Pad | Soldered | ZeroWriter |
|---|---|---|
| 17–22 | `unconnected-(U11-Pad17…22)` | `unconnected-(U11-SD2/SD3/CMD/CLK/SD0/SD1-Pad…)` |

ZeroWriter's naming is more informative and confirms what those pads are: the WROVER's **SDIO/flash interface** (`SD0`–`SD3`, `CMD`, `CLK`), brought out on the module footprint but unusable.

**Practical conclusion: firmware targeting a stock Inkplate 5 Gen 2 will find the same pins on a ZeroWriter Ink main board.** The Inkplate Arduino library applies. What differs is *off*-processor — charging (switch-mode [`BQ25306`](../../../components/texas-instruments/bq25306/README.md) vs linear `MCP73831T`), [USB-C](../../../components/generic/usb-c-interface/README.md) and [microSD](../../../components/generic/micro-sd-sdmmc/README.md) relocated to a breakout PCB, and an added 16-pin inter-board connector.

## Known uses

- **[ZeroWriter Ink](../../zerowriter/zerowriter-ink/README.md)** — ships a *respun* variant of this board with a switch-mode [`BQ25306`](../../../components/texas-instruments/bq25306/README.md) charger replacing the linear `MCP73831T`, [USB-C](../../../components/generic/usb-c-interface/README.md) and [microSD](../../../components/generic/micro-sd-sdmmc/README.md) relocated to a separate breakout PCB, and a 16-pin inter-board connector added. The panel, processor, PMIC, expander and RTC are unchanged, so the Inkplate Arduino library applies. Note the Ink also carries a **second processor** — an [ESP32-WROOM-32U](../../../components/espressif/esp32-wroom-32u/README.md) on its keyboard PCB — which has no counterpart on this board.

## Artifacts

```
artifacts/hardware/soldered-inkplate-5-gen2-hardware-design/   TAPR OHL
                                                commit 7450a321 (2025-03-08)
├── CAD/V1.1.0/       KiCad hierarchical sheets + .kicad_pcb + panel
├── OUTPUTS/V1.1.0/   BOM.csv, Schematics.pdf, iBOM.html, gerbers, 3D .step
└── OUTPUTS/Compliance/  CE, UKCA, safety sheets
```

Software, examples and the full e-paper interface description are shared with the Inkplate 5 — see [`../inkplate-5/README.md`](../inkplate-5/README.md) and [Peripheral Mode](../inkplate-5/features/peripheral-mode.md).

## Related

- [Source manifest](sources.md) — Gen-2-specific sources; the shared base is in [`../inkplate-5/sources.md`](../inkplate-5/sources.md)
- [Inkplate 5 (both generations, full record)](../inkplate-5/README.md) · [its component index](../inkplate-5/README.md#component-records)
- [Pinouts and buses](../inkplate-5/pinouts-and-buses.md) — verified to apply to this board unmodified
- [Soldered Electronics vendor guide](../../../vendors/soldered-electronics/README.md)
- [ZeroWriter Ink](../../zerowriter/zerowriter-ink/README.md)
- [Component index](../../../components/README.md) · [Device index](../../README.md)

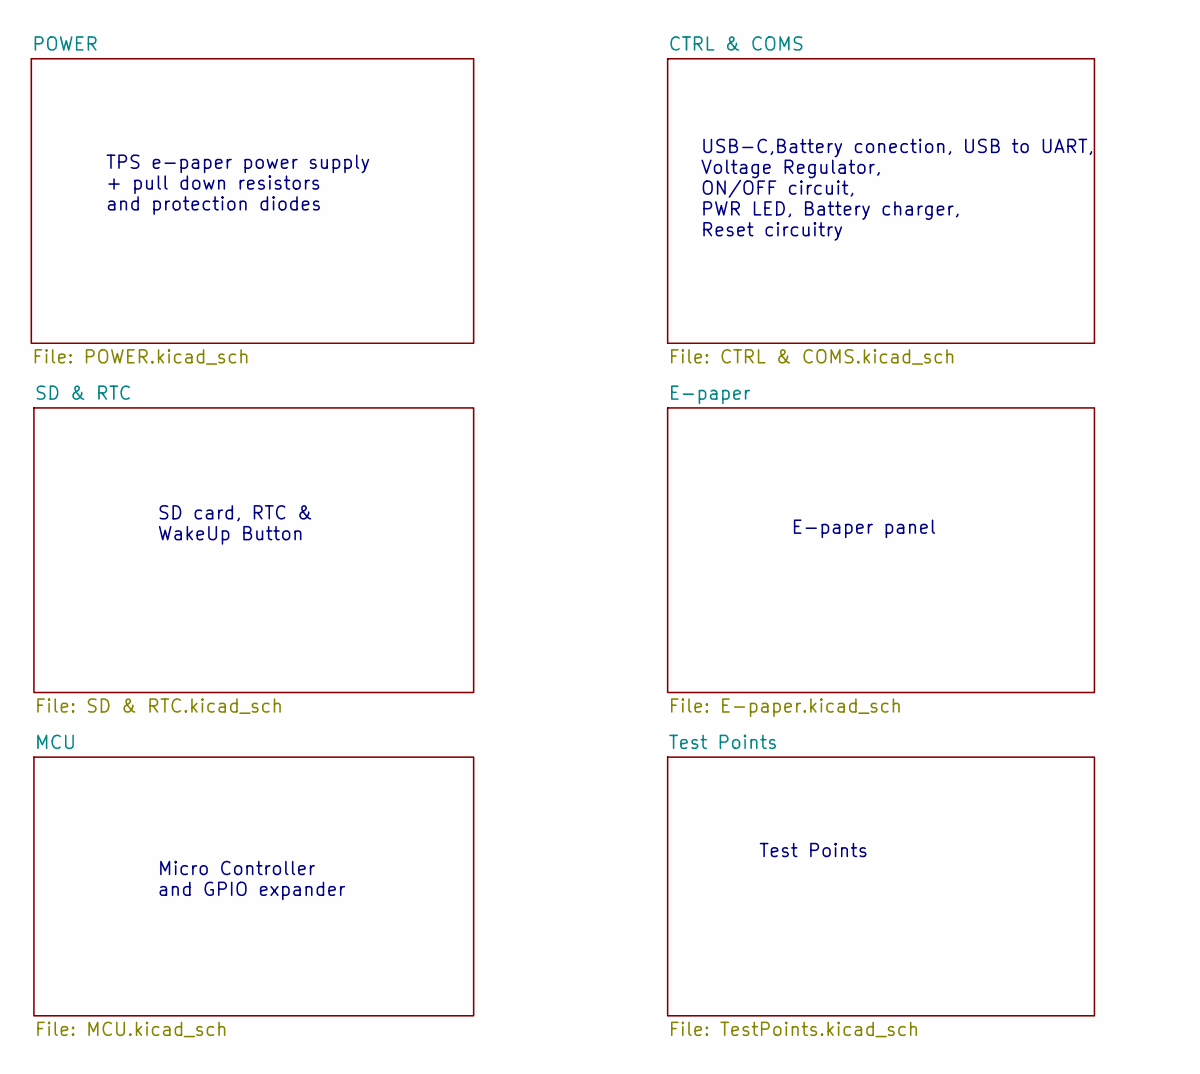
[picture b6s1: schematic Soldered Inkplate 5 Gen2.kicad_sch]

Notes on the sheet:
Test Points
USB-C,Battery conection, USB to UART, Voltage Regulator, ON/OFF circuit, PWR LED, Battery charger, Reset circuitry
SD card, RTC & WakeUp Button
Micro Controller and GPIO expander
TPS e-paper power supply + pull down resistors and protection diodes
E-paper panel

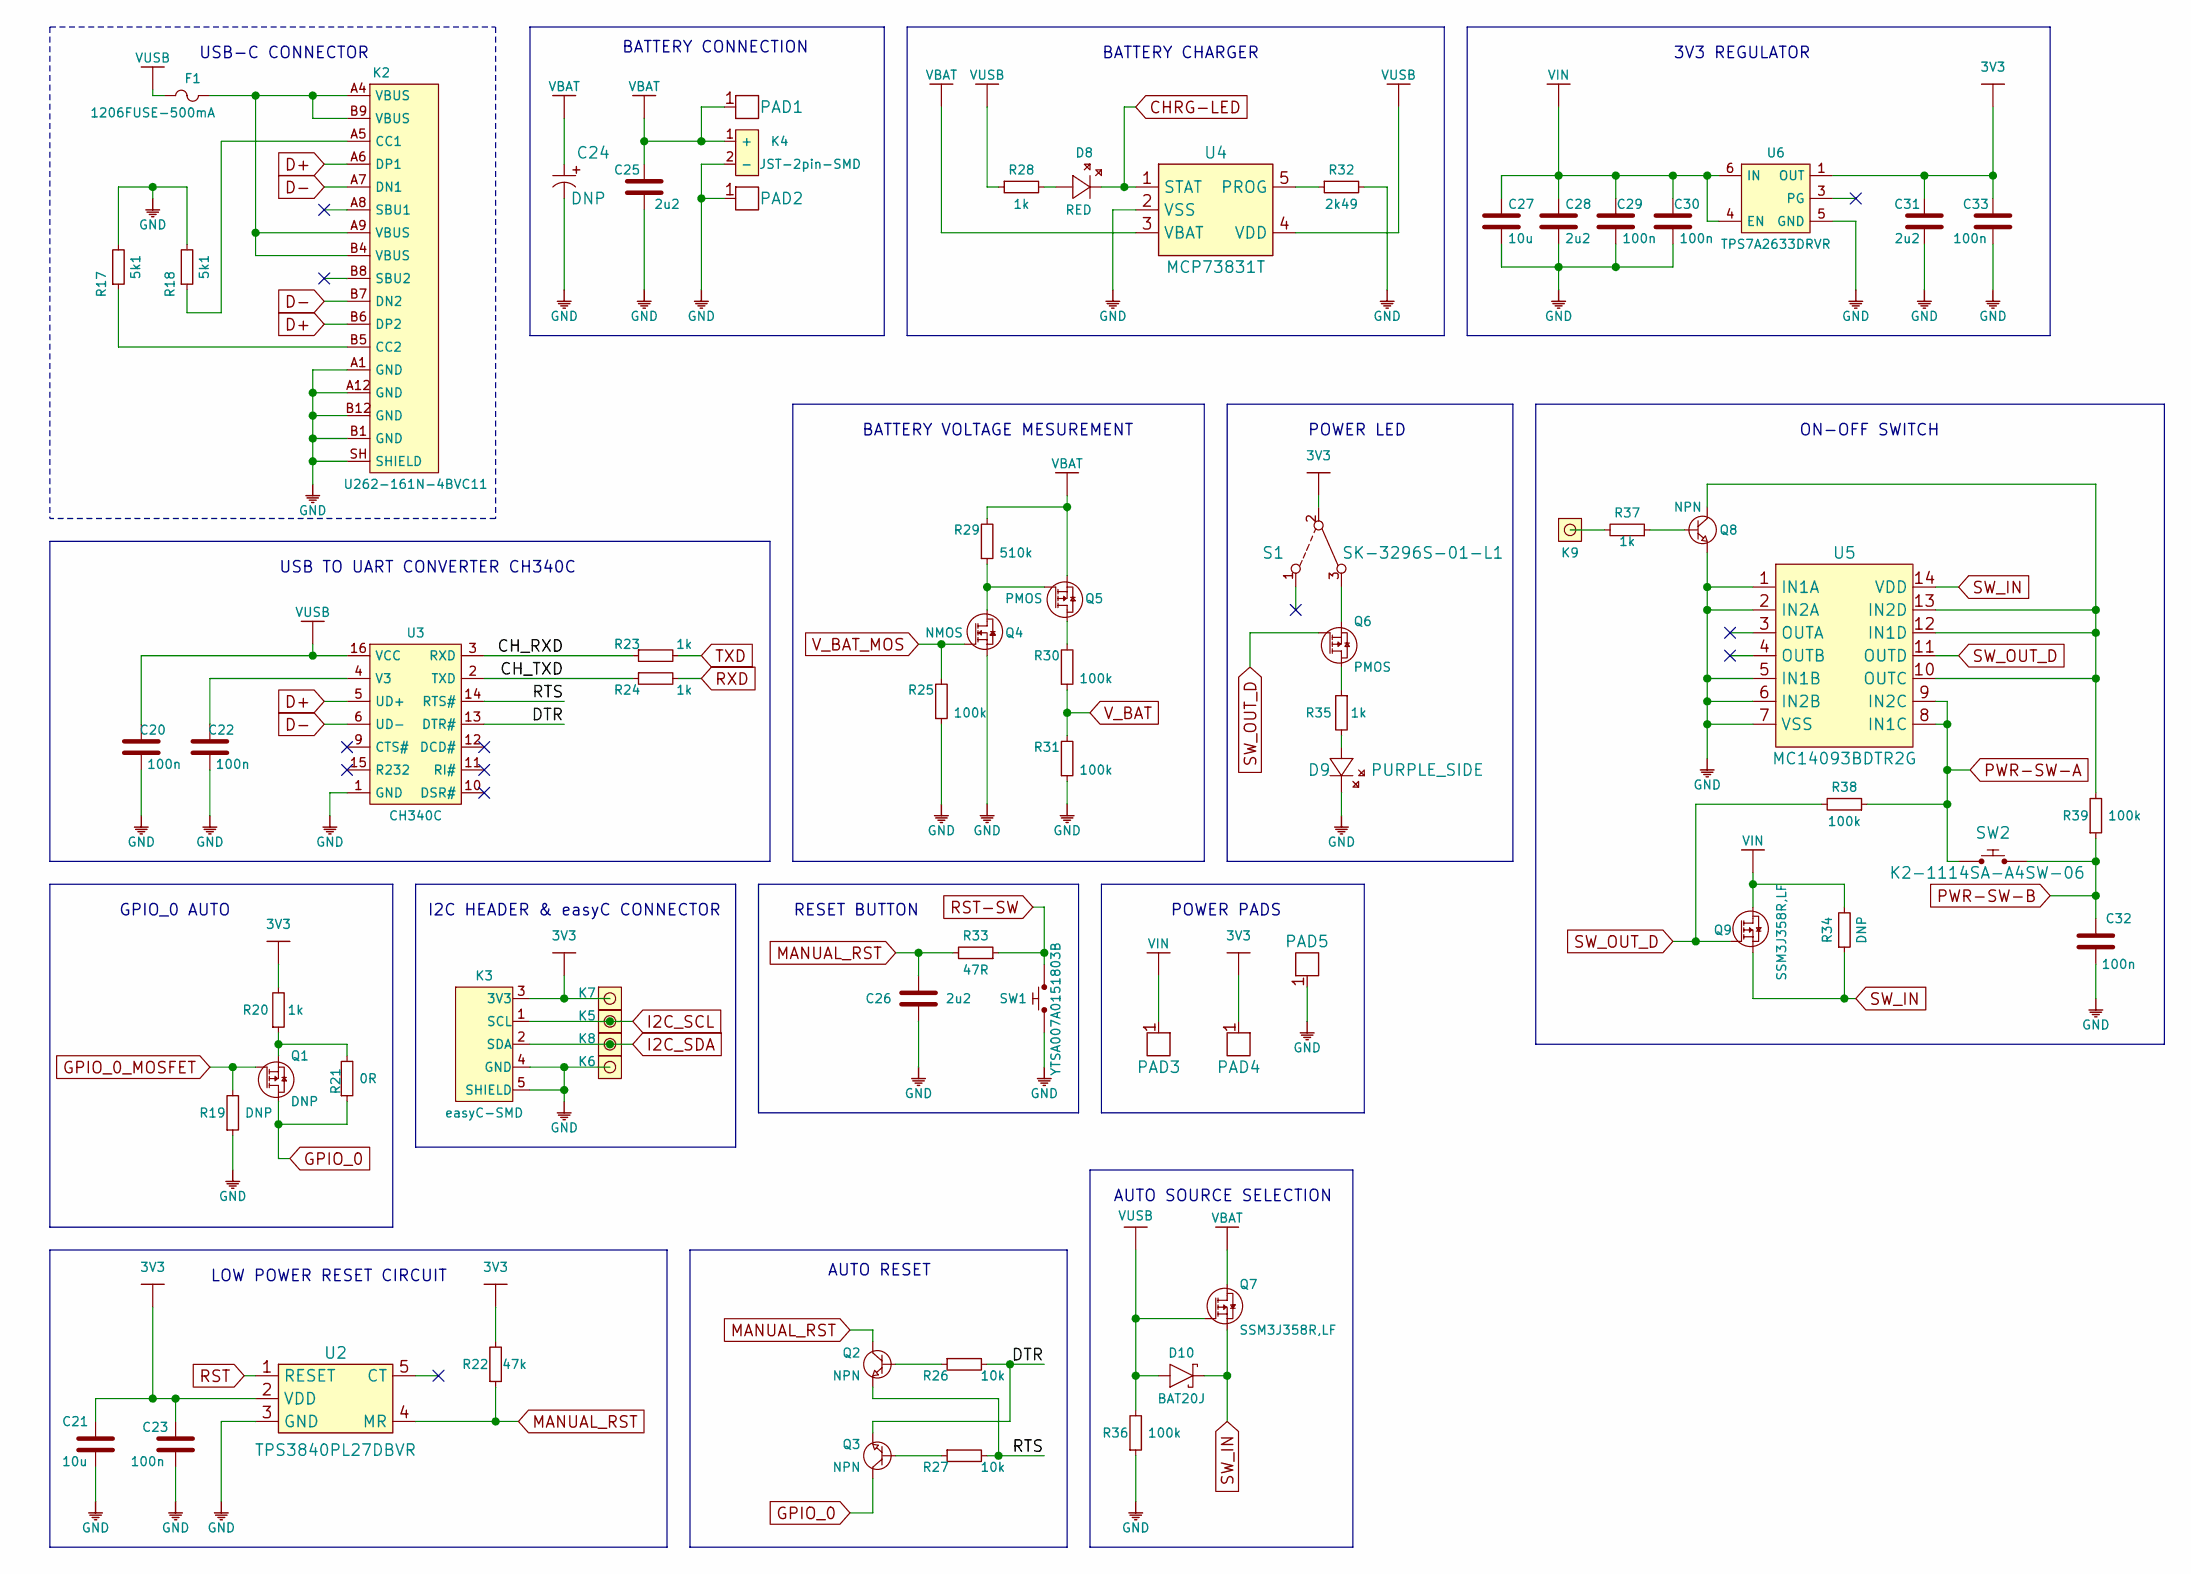
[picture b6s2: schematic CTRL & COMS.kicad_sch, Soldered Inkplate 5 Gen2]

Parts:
C20, C22, C23, C29, C30, C32, C33: 100n; 0603C
C21, C27: 10u; 1206C
C24: DNP; 2917C
C25, C26, C28, C31: 2u2; 0603C
D8: RED; 0402LED
D9: PURPLE_SIDE; LTST-S270GKT
D10: BAT20J; SOD-323
F1: 1206FUSE-500mA; 1206FUSE
K2: U262-161N-4BVC11
K3: easyC-SMD; easyC-connector
K4: JST-2pin-SMD
K5, K6, K7, K8, K9: HEADER_MALE_1X1_Inkplate
PAD1, PAD2, PAD3, PAD4, PAD5: PAD_4x4
Q1: DNP; SOT-23-3
Q2, Q3, Q8: NPN; SOT-23-3
Q4: NMOS; SOT-23-3
Q5, Q6: PMOS; SOT-23-3
Q7, Q9: SSM3J358R,LF; SOT-23-3
R17, R18: 5k1; 0603R
R19, R34: DNP; 0603R
R20, R23, R24, R28, R35, R37: 1k; 0603R
R21: 0R; 0603R
R22: 47k; 0603R
R25, R30, R31, R36, R38, R39: 100k; 0603R
R26, R27: 10k; 0603R
R29: 510k; 0603R
R32: 2k49; 0603R
R33: 47R; 0603R
S1: SK-3296S-01-L1
SW1: YTSA007A0151803B
SW2: K2-1114SA-A4SW-06
U2: TPS3840PL27DBVR; SOT-23-5
U3: CH340C; SOP-16
U4: MCP73831T; SOT-23-5
U5: MC14093BDTR2G; TSSOP-14
U6: TPS7A2633DRVR

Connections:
3V3: C21.2, C23.2, C31.2, C33.2, K3.3 (3V3), K7.1, PAD4.1, R20.2, R22.2, S1.2, U2.2 (VDD), U6.1 (OUT); also elsewhere on the board
/CTRL & COMS/CH_RXD: R23.1, U3.3 (RXD)
/CTRL & COMS/CH_TXD: R24.1, U3.2 (TXD)
/CTRL & COMS/DTR: Q3.2 (E), R26.2, U3.13 (DTR#)
/CTRL & COMS/RTS: Q2.2 (E), R27.2, U3.14 (RTS#)
CHRG-LED: D8.2 (K), U4.1 (STAT); also elsewhere on the board
D+: K2.A6 (DP1), K2.B6 (DP2), U3.5 (UD+); also elsewhere on the board
D-: K2.A7 (DN1), K2.B7 (DN2), U3.6 (UD-); also elsewhere on the board
GND: C20.1, C21.1, C22.1, C23.1, C24.2 (-), C25.1, C26.1, C27.1, C28.1, C29.1, C30.1, C31.1, C32.1, C33.1, D9.2 (K), K2.A1 (GND), K2.A12 (GND), K2.B1 (GND), K2.B12 (GND), K2.SH (SHIELD), K3.4 (GND), K3.5 (SHIELD), K4.2 (-), K6.1, PAD2.1, PAD5.1, Q4.2 (S), Q8.2 (E), R17.2, R18.2, R19.1, R25.1, R31.1, R32.2, R36.1, SW1.1, U2.3 (GND), U3.1 (GND), U4.2 (VSS), U5.1 (IN1A), U5.2 (IN2A), U5.5 (IN1B), U5.6 (IN2B), U5.7 (VSS), U6.5 (GND); also elsewhere on the board
GPIO_0: Q1.3 (D), Q3.3 (C), R21.1; also elsewhere on the board
GPIO_0_MOSFET: Q1.1 (G), R19.2; also elsewhere on the board
I2C_SCL: K3.1 (SCL), K5.1; also elsewhere on the board
I2C_SDA: K3.2 (SDA), K8.1; also elsewhere on the board
MANUAL_RST: C26.2, Q2.3 (C), R22.1, R33.2, U2.4 (MR); also elsewhere on the board
unnamed: C22.2, U3.4 (V3)
unnamed: D9.1 (A), R35.2
unnamed: F1.2, K2.A4 (VBUS), K2.A9 (VBUS), K2.B4 (VBUS), K2.B9 (VBUS)
unnamed: K2.A5 (CC1), R18.1
unnamed: K2.B5 (CC2), R17.1
unnamed: K9.1, R37.2
unnamed: Q1.2 (S), R20.1, R21.2
unnamed: Q2.1 (B), R26.1
unnamed: Q3.1 (B), R27.1
unnamed: Q4.3 (D), Q5.1 (G), R29.1
unnamed: Q5.3 (D), R30.2
unnamed: Q6.2 (S), S1.3
unnamed: Q6.3 (D), R35.1
unnamed: Q8.1 (B), R37.1
unnamed: Q8.3 (C), R39.2, U5.10 (OUTC), U5.12 (IN1D), U5.13 (IN2D)
unnamed: D8.1 (A), R28.2
unnamed: R32.1, U4.5 (PROG)
PWR-SW-A: R38.1, SW2.1, U5.8 (IN1C), U5.9 (IN2C); also elsewhere on the board
PWR-SW-B: C32.2, R39.1, SW2.2; also elsewhere on the board
RST: U2.1 (RESET); also elsewhere on the board
RST-SW: R33.1, SW1.2; also elsewhere on the board
RXD: R24.2; also elsewhere on the board
SW_IN: D10.2 (C), Q7.2 (S), Q9.2 (S), R34.1, U5.14 (VDD); also elsewhere on the board
SW_OUT_D: Q6.1 (G), Q9.1 (G), R38.2, U5.11 (OUTD); also elsewhere on the board
TXD: R23.2; also elsewhere on the board
VBAT: C24.1 (+), C25.2, K4.1 (+), PAD1.1, Q5.2 (S), Q7.3 (D), R29.2, U4.3 (VBAT); also elsewhere on the board
VIN: C27.2, C28.2, C29.2, C30.2, PAD3.1, Q9.3 (D), R34.2, U6.4 (EN), U6.6 (IN); also elsewhere on the board
VUSB: C20.2, D10.1 (A), F1.1, Q7.1 (G), R28.1, R36.2, U3.16 (VCC), U4.4 (VDD); also elsewhere on the board
V_BAT: R30.1, R31.2; also elsewhere on the board
V_BAT_MOS: Q4.1 (G), R25.2; also elsewhere on the board

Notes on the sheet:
LOW POWER RESET CIRCUIT
AUTO RESET
GPIO_0 AUTO
ON-OFF SWITCH
BATTERY VOLTAGE MESUREMENT
AUTO SOURCE SELECTION
RESET BUTTON
USB-C CONNECTOR
I2C HEADER & easyC CONNECTOR
BATTERY CHARGER
USB TO UART CONVERTER CH340C
POWER LED
BATTERY CONNECTION
3V3 REGULATOR
POWER PADS
